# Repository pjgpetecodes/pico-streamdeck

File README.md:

# Pico Producer

## About this Project

This project is an OBS Controller using a Raspberry Pi Pico and CircuitPython.

# In Action

# Featured

The Raspberry Pi Pico Producer has been featured in the following publications;

- Raspberry Pi Website: https://www.raspberrypi.org/documentation/rp2040/getting-started/
- Hackster: https://www.hackster.io/news/pete-gallagher-s-raspberry-pi-pico-stream-deck-aids-obs-work-via-a-smart-circuitpython-script-0df423724379
- Hackster: https://www.hackster.io/news/use-a-raspberry-pi-pico-to-build-your-own-affordable-stream-deck-a0ad237f0d25
- Hackaday: https://hackaday.com/2021/02/23/lighted-raspberry-pico-stream-deck-is-easy-as-pi/
- OSH Park: https://blog.oshpark.com/2021/03/08/obs-controller-using-circuitpython-on-rpi-pico/

## Basic Circuit

I've avoid GP15 as it's assigned a USB function... Using GP15 results in the following error at startup;

"ValueError: GP15 in use"

# PCB

Front

Back

PCB

You can have your PCB made at OSH Park here;

https://oshpark.com/shared_projects/UNP0qi2U

# Parts List

| Part | Qty | Link |
|------|-----|------|
| PCB | 1 | https://oshpark.com/shared_projects/UNP0qi2U |
| Cherry MX Keycaps | 12 | https://amzn.to/2Oo1nLP |
| 3mm LED | 12 | https://amzn.to/3rAqNEV |
| 220 Ohm 8x Isolated Resistor Pack | 2 | http://bit.ly/picoproducerresistorarray |
| Raspberry Pi Pico | 1 | http://bit.ly/pimoroni-pico |
| 20 pin Male PCB Header | 2 | https://amzn.to/3sUr8lN |
| 3D Printed Case | 1 | https://www.thingiverse.com/thing:4800253 |

Notes: 

- You can feel free to use 12 individual 220 Ohm Resistors - https://amzn.to/3qqaWai
- If you wire this without a PCB then use the following wire from Pimoroni - http://bit.ly/pimoroni-rainbow-wire

# Case

We now have two different case designs....

Cliff Agius and his son have created a version of the box suited for buttons with holes for LEDs.

I've modified this design to add LEDs above each button;

It was originally based on this design;

https://www.thingiverse.com/thing:4186055

The keycaps are from here;

https://www.thingiverse.com/thing:4186055

You can find the project on Thingiverse here;

https://www.thingiverse.com/thing:4800253

# Assembly Hints

- Insert the 20 Pin PCB headers with the long legs away from the PCB towards the Pico (Otherwise it'll fowl the faceplate)
- Solder the 2 Resistor Packs and the Pico PCB Headers first. Then the LEDs and Buttons. Then the Pico.
- You'll need to trim the legs on the resistor packs which border the three left hand buttons.
- Insert the LEDs into the PCB, then insert the Buttons into the faceplate and then insert that into the PCB.
- Push the leds back through the PCB, so they poke into the holes in the faceplate, otherwise they'll be below the faceplate.
- You'll need to trim the legs on the PCB headers otherwise it'll fowl the bottom of the case.

# CircuitPython HID

You can find some more info about the CircuitPython KeyMappings here;

https://circuitpython.readthedocs.io/projects/hid/en/latest/_modules/adafruit_hid/keycode.html

## Instructions

- Plug in the Raspberry Pi Pico while holding the onboard button.
- Your PC will mount the Pico as a drive
- Copy the `adafruit-circuitpython-raspberry_pi_pico-en_US-6.2.0-beta.1.uf2` file to the Pico
- The Pico will reboot once it's done with CircuitPython onboard.
- Copy the `adafruit_hid` folder and the `code.py` file to the Pico
- In OBS setup Hotkeys for the different scenes by putting your cursor in the Hotkey Box and pressing a button...

```
Scene 1 =  ctrl + F1
Scene 2 =  ctrl + F2
Scene 3 =  ctrl + F3
Scene 4 =  ctrl + F4
Scene 5 =  ctrl + F5
Scene 6 =  ctrl + F6
Scene 7 =  ctrl + F7
Scene 8 =  ctrl + F8
Scene 9 =  ctrl + F9
Scene 10 =  ctrl + F10
Scene 11 =  ctrl + F11
Scene 12 =  ctrl + F12
```

- Press the buttons to change scenes in OBS!
- Each button will light a corresponding LED to show which Scene is currently active.

## Debugging

Circuit Python creates a virtual COM port, so you can use a terminal Program set to 8N1 9600 Baud to debug the code... Just hit the enter key at teh prompt, and the terminal will echo there.

It might help to put a large enough delay at the start of your code to give you time to initialise the terminal.

## Future Planning

- Look at Bluetooth / WebSockets (Will need add on circuitary!)
- Possible Matrix Input (But, I like the simplicity)
- Possible Resistor Ladder Input (But, again, I like the simplicity)

## Notes

The HID control code is based on a nice blog post by Hriday which shows how to get the Pico working as a HID device, emulating a keyboard;

https://hridaybarot.home.blog/2021/01/31/using-raspberry-pi-pico-has-hid-device-to-control-mouse-and-keyboard/

## Thanks

Thanks to Cliff Agius and his son for the original 3d Files.
Thanks to John Furcean for refactoring the code.
Thanks to frankalicious for fixing some spelling checks.

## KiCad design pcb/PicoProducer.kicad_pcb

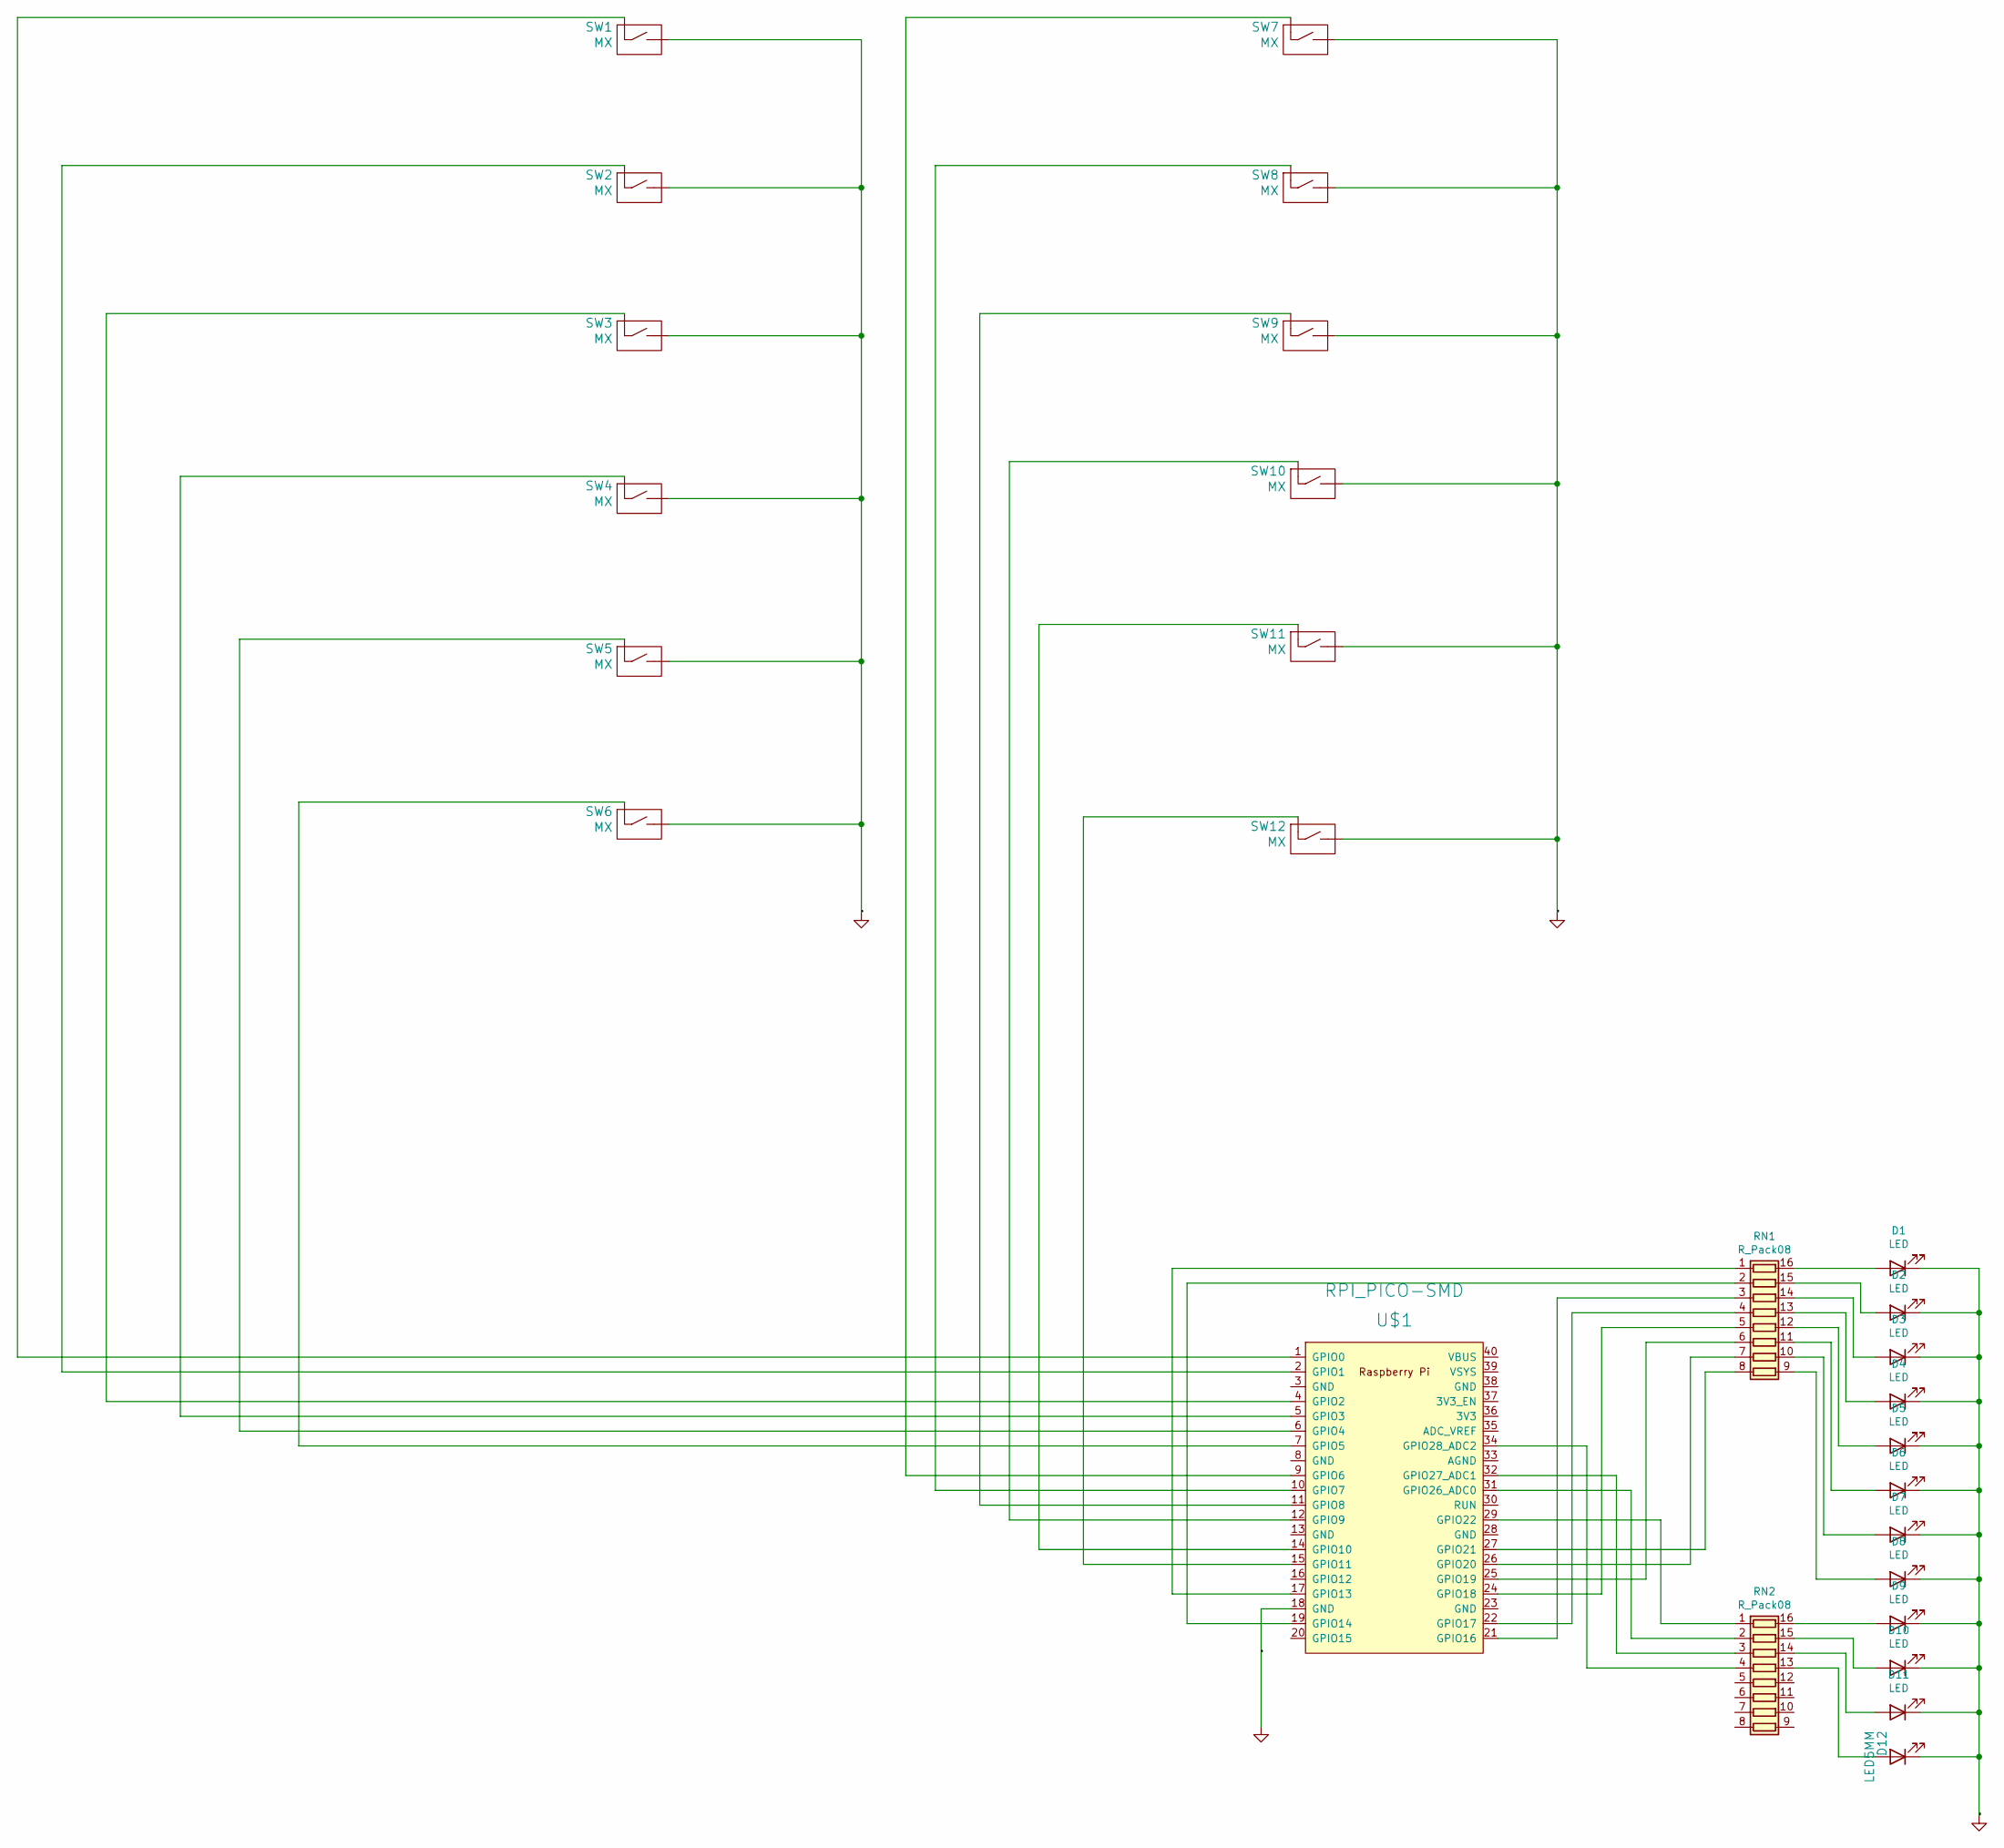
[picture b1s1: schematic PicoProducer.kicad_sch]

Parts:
D1, D2, D3, D4, D5, D6, D7, D8, D9, D10, D11: LED; LED_D5.0mm
D12: LED5MM; LED_D5.0mm
RN1, RN2: R_Pack08; DIP-16_W7.62mm
SW1, SW3, SW4, SW5, SW6, SW7, SW8, SW9, SW10, SW11, SW12: MX; SW_Cherry_MX_PCB_1.00u
SW2: MX; SW_Cherry_MX_Plate_1.00u
U$1: RPI_PICO-SMD; RPi_Pico_SMD_TH

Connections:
GND: D1.1 (K), D2.1 (K), D3.1 (K), D4.1 (K), D5.1 (K), D6.1 (K), D7.1 (K), D8.1 (K), D9.1 (K), D10.1 (K), D11.1 (K), D12.1 (K), SW1.2 (B), SW2.2 (B), SW3.2 (B), SW4.2 (B), SW5.2 (B), SW6.2 (B), SW7.2 (B), SW8.2 (B), SW9.2 (B), SW10.2 (B), SW11.2 (B), SW12.2 (B), U$1.18 (GND)
unnamed: D1.2 (A), RN1.16 (R1.2)
unnamed: D2.2 (A), RN1.15 (R2.2)
unnamed: D3.2 (A), RN1.14 (R3.2)
unnamed: D4.2 (A), RN1.13 (R4.2)
unnamed: D5.2 (A), RN1.12 (R5.2)
unnamed: D6.2 (A), RN1.11 (R6.2)
unnamed: D7.2 (A), RN1.10 (R7.2)
unnamed: D8.2 (A), RN1.9 (R8.2)
unnamed: D9.2 (A), RN2.16 (R1.2)
unnamed: D10.2 (A), RN2.15 (R2.2)
unnamed: D11.2 (A), RN2.14 (R3.2)
unnamed: D12.2 (A), RN2.13 (R4.2)
unnamed: RN1.1 (R1.1), U$1.17 (GPIO13)
unnamed: RN1.2 (R2.1), U$1.19 (GPIO14)
unnamed: RN1.3 (R3.1), U$1.21 (GPIO16)
unnamed: RN1.4 (R4.1), U$1.22 (GPIO17)
unnamed: RN1.5 (R5.1), U$1.24 (GPIO18)
unnamed: RN1.6 (R6.1), U$1.25 (GPIO19)
unnamed: RN1.7 (R7.1), U$1.26 (GPIO20)
unnamed: RN1.8 (R8.1), U$1.27 (GPIO21)
unnamed: RN2.1 (R1.1), U$1.29 (GPIO22)
unnamed: RN2.2 (R2.1), U$1.31 (GPIO26_ADC0)
unnamed: RN2.3 (R3.1), U$1.32 (GPIO27_ADC1)
unnamed: RN2.4 (R4.1), U$1.34 (GPIO28_ADC2)
unnamed: SW1.1 (A), U$1.1 (GPIO0)
unnamed: SW2.1 (A), U$1.2 (GPIO1)
unnamed: SW3.1 (A), U$1.4 (GPIO2)
unnamed: SW4.1 (A), U$1.5 (GPIO3)
unnamed: SW5.1 (A), U$1.6 (GPIO4)
unnamed: SW6.1 (A), U$1.7 (GPIO5)
unnamed: SW7.1 (A), U$1.9 (GPIO6)
unnamed: SW8.1 (A), U$1.10 (GPIO7)
unnamed: SW9.1 (A), U$1.11 (GPIO8)
unnamed: SW10.1 (A), U$1.12 (GPIO9)
unnamed: SW11.1 (A), U$1.14 (GPIO10)
unnamed: SW12.1 (A), U$1.15 (GPIO11)

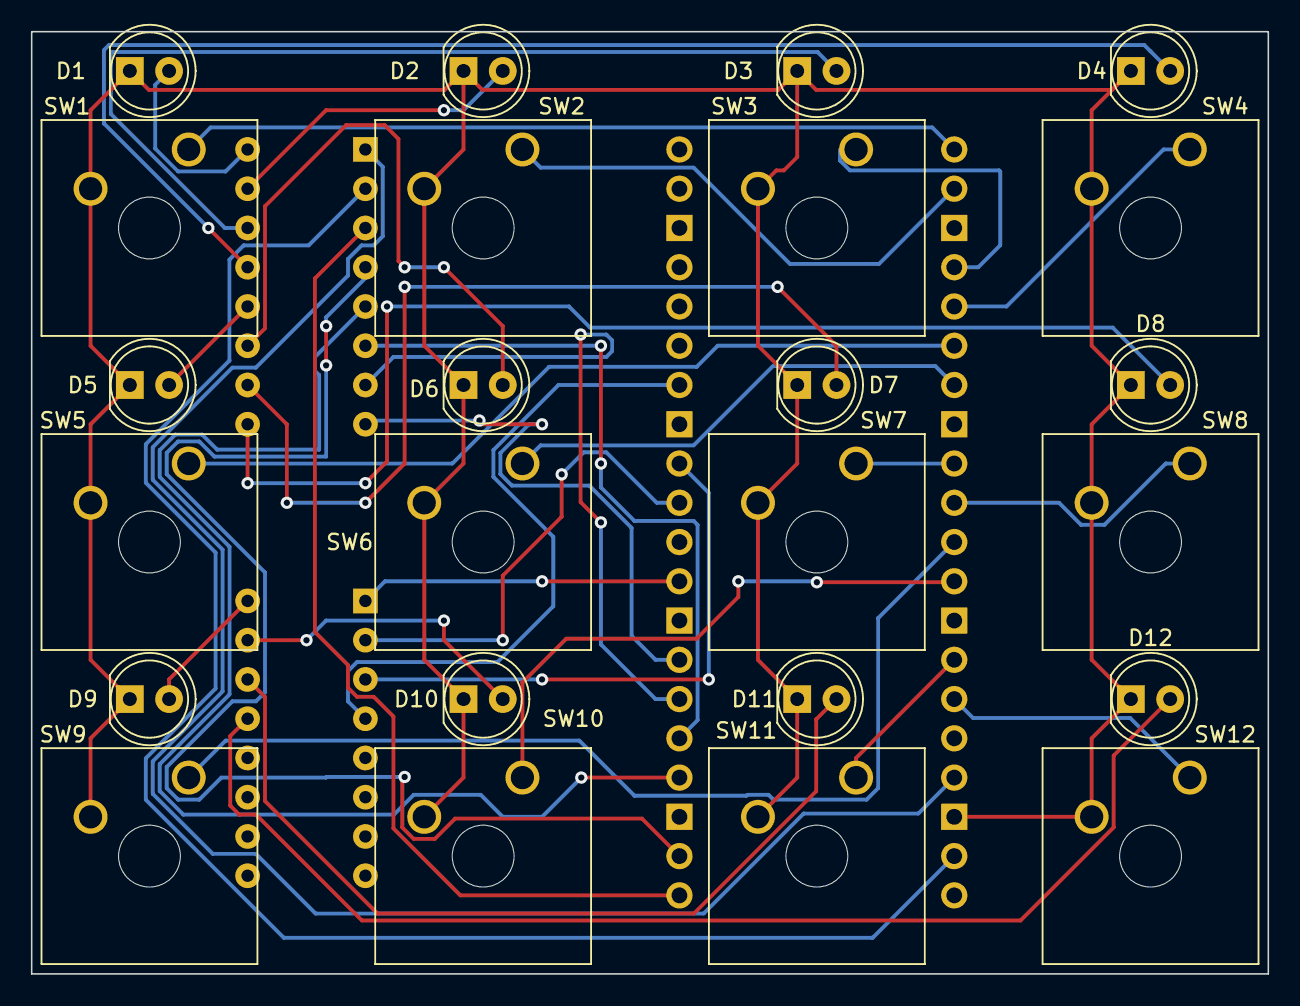
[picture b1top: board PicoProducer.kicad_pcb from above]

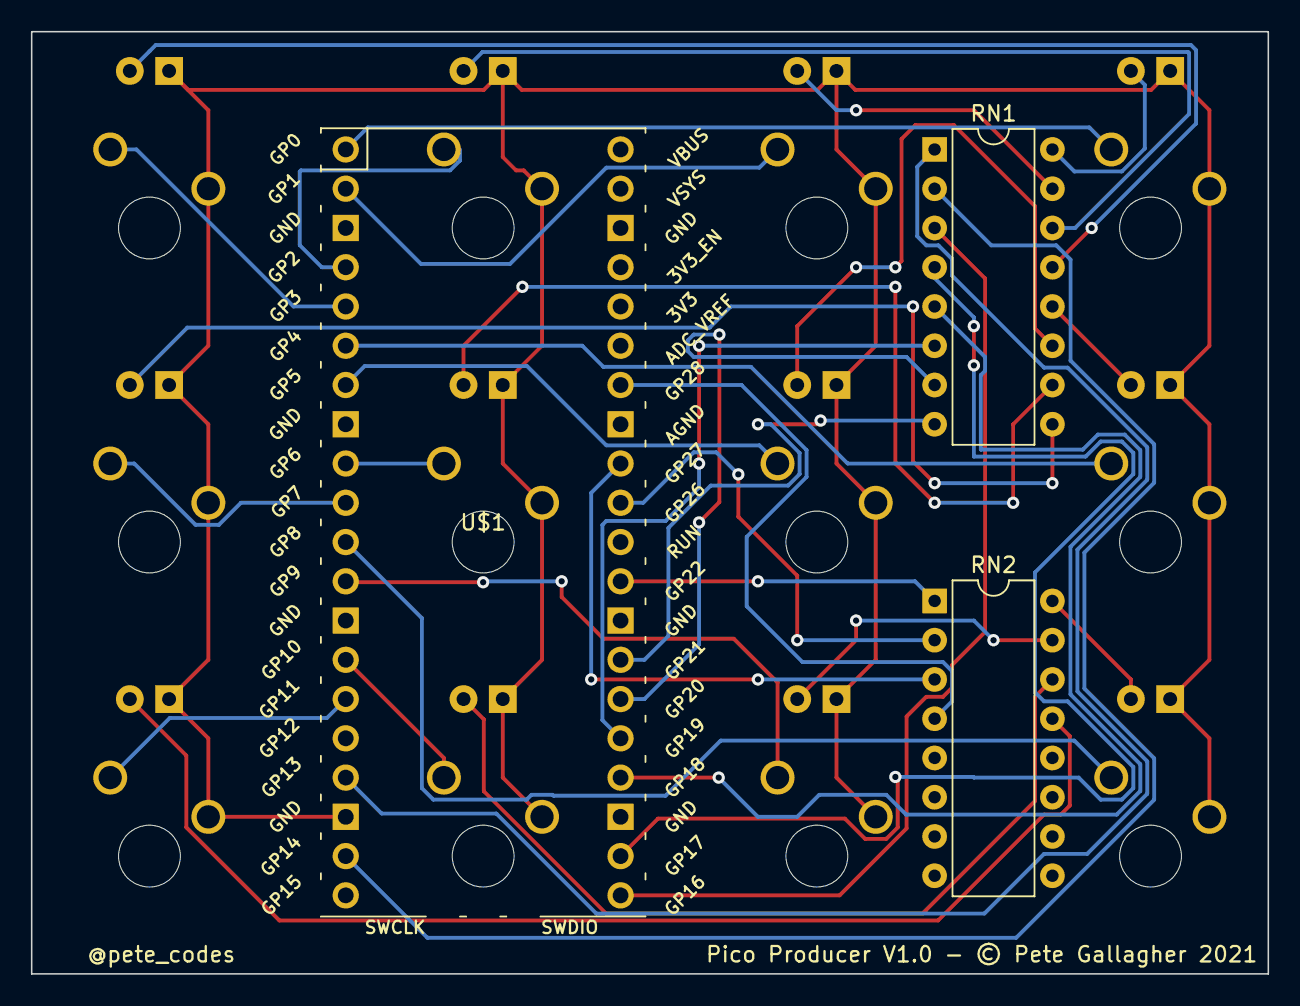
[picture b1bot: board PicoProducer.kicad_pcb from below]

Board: 2 copper layers, 80.0 x 61.0 mm, 27 parts (3 on the bottom side), 37 nets.

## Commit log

2021-02-04 Origin
2021-02-04 Tidy Code
2021-02-04 Added image and circuit
2021-02-04 Added future planning to README
2021-02-06 Added crude LED Control to each button
2021-02-08 Added Extra Buttons and delay between Press and Release
2021-02-08 Added and Updated Circuit
2021-02-08 Updated Circuit Colours
2021-02-08 Updated Instructions
2021-02-08 Added Gif to Readme
2021-02-11 Added extra buttons and LEDs
2021-02-11 Added Comments
2021-02-11 LED 3d Files added
2021-02-11 Switched to Embossed Logo
2021-02-11 Added 3d model to README
2021-02-11 Added Cliff's 3D Files
2021-02-11 Removed Box from Planning
2021-02-11 Changed Name
2021-02-11 Added KeyCaps
2021-02-11 Changed wording
2021-02-12 refactor code.py
2021-02-12 Don't use Pin15 - USB Conflict! "ValueError: GP15 in use"
2021-02-12 Added Debugging Info
2021-02-12 remove GP15 from being used
2021-02-12 Added extra buttons and LEDs to Circuit
2021-02-12 remote sleep after keycode send
2021-02-12 switch from keyboard.send to keyboard.press and keyboard.release
2021-02-12 switch keycodes to using ALT + F1-12
2021-02-12 Added new Finished project and decals
2021-02-13 Added more Future Planning
2021-02-25 fix spelling errors
2021-03-06 Added PCB, latest Circuit, Code and Key Decals
2021-03-06 Add Parts List and Assembly hints to Readme
2021-03-06 Updated 3D Model Image etc
2021-03-06 Add new images etc
2021-03-06 Fix Spelling
2021-03-18 Fix issue with code.py
2021-03-20 Added Features to README
2021-03-20 Added PCB and Case Links
2021-03-20 Added OSH Park and Thingiverse Links
2021-05-03 Reduced size of keycap to prevent catching
2025-05-28 fixed models for printing. top plate and full case.

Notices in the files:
pcb/PicoProducer.kicad_pcb:
Pico Producer V1.0 - © Pete Gallagher 2021
